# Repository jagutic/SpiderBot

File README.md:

# Spider
Proyecto final Mecatrónica

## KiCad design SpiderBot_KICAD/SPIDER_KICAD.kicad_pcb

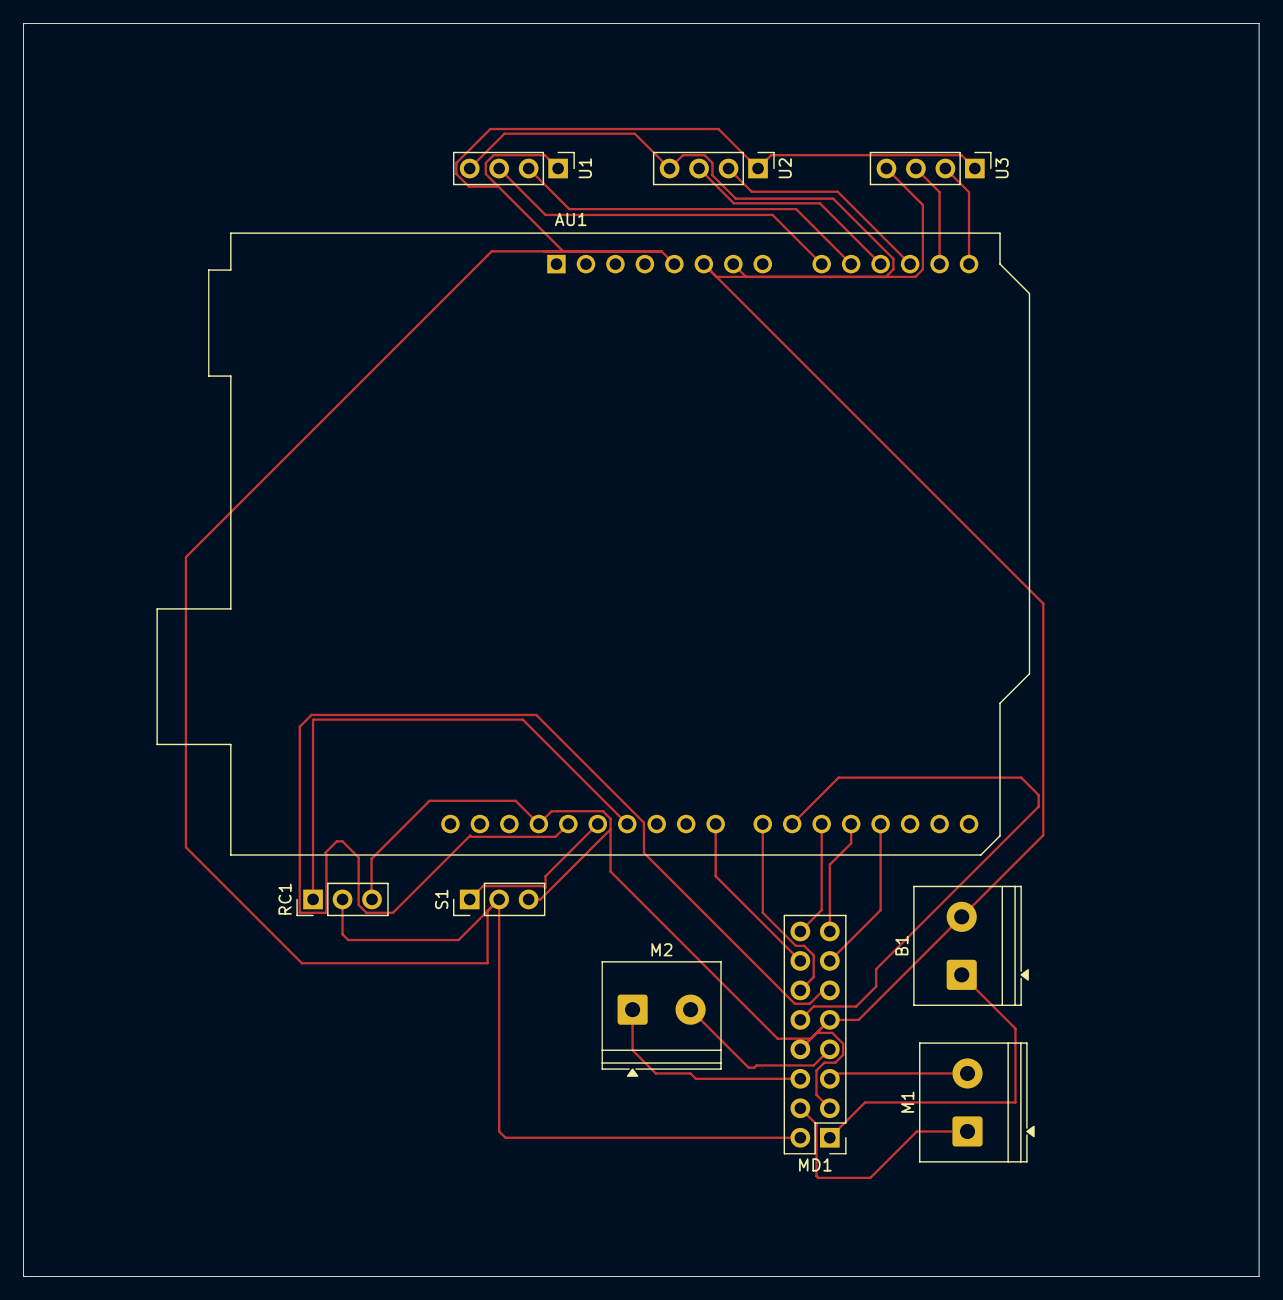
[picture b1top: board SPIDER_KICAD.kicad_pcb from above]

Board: 2 copper layers, 106.5 x 108.0 mm, 10 parts (0 on the bottom side), 22 nets.

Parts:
AU1: Arduino_UNO_R3
B1: Battery; TerminalBlock_Phoenix_PT-1,5-2-5.0-H_1x02_P5.00mm_Horizontal
M1, M2: Motor; TerminalBlock_Phoenix_PT-1,5-2-5.0-H_1x02_P5.00mm_Horizontal
MD1: Motor Driver (TB6612FNG); PinHeader_2x08_P2.54mm_Vertical
RC1: Remote Controller; PinHeader_1x03_P2.54mm_Vertical
S1: Servomotor; PinHeader_1x03_P2.54mm_Vertical
U1, U2, U3: Ultrasonic Sensor (HC-SR04); PinHeader_1x04_P2.54mm_Vertical

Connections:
+5V: AU1.5 (+5V), MD1.2, RC1.2, S1.2, U1.1, U2.1, U3.1
AIN1: AU1.23 (D8), MD1.14
AIN2: AU1.19 (D4), MD1.15
BIN1: AU1.18 (D3), MD1.13
BIN2: AU1.28 (D13), MD1.11
ECHO1: AU1.9 (A0), U1.3
ECHO2: AU1.11 (A2), U2.3
ECHO3: AU1.13 (SDA/A4), U3.3
GND: AU1.6 (GND), AU1.7 (GND), AU1.29 (GND), B1.2, MD1.3, MD1.8, MD1.9, RC1.3, S1.3, U1.4, U2.4, U3.4
IR_DATA: AU1.26 (D11), RC1.1
MSTBY: AU1.22 (D7), MD1.12
unnamed: M1.1, MD1.4
unnamed: M1.2, MD1.5
unnamed: M2.1, MD1.6
unnamed: M2.2, MD1.7
PWMA: AU1.20 (D5), MD1.16
PWMB: AU1.21 (D6), MD1.10
SERVO_PWM: AU1.27 (D12), S1.1
TRIG1: AU1.10 (A1), U1.2
TRIG2: AU1.12 (A3), U2.2
TRIG3: AU1.14 (SCL/A5), U3.2
V_BATT: B1.1, MD1.1

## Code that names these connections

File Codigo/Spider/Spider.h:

#ifndef SPIDER_H
#define SPIDER_H

#include <Servo.h>

// PINS
#define PWMA 5
#define AIN1 8
#define AIN2 4
#define PWMB 6
#define BIN1 3
#define BIN2 13
#define MOTORS_STBY 7
#define SERVO_HEAD 12

// Ultrasound sensors
#define ECHO_HEAD A0
#define TRIG_HEAD A1
#define ECHO_LEFT A2
#define TRIG_LEFT A3
#define ECHO_RIGHT A4
#define TRIG_RIGHT A5
#define MAX_DISTANCE 400.0 // cm
#define MIN_DISTANCE 2.0 // cm

// CONSTANTS
#define SPEED_MOVE 200
#define SPEED_TURN 255
#define SPEED_TURN_FACTOR 0.9
#define INIT_ANGLE 75


// Movement
const int MOTOR_LEFT[3] = {AIN2, AIN1, PWMA};
const int MOTOR_RIGHT[3] = {BIN1, BIN2, PWMB};

enum direction {
  FORWARD = 0,
  BACKWARD,
  LEFT,
  RIGHT,
};


// Class of our robot
class Spider {
private:
  Servo servo;

  // FUNCTIONS
  // Return distance in cm
  float get_dist(int trig, int echo) {
    // Clean
    digitalWrite(trig, LOW);
    delayMicroseconds(2);

    // Send trig
    digitalWrite(trig, HIGH);
    delayMicroseconds(10);
    digitalWrite(trig, LOW);

    // Calculate distance
    float duration = pulseIn(echo, HIGH, 30000);
    float dist = duration * 0.034 / 2;

    //Return error with very low values
    // or with very HIGH ones
    if (dist < MIN_DISTANCE || dist > MAX_DISTANCE) {
      //dist = get_dist(trig, echo);
      return MAX_DISTANCE;
    }

    // Reactivate when valid dist is obtained
    return dist;
  }

public:
  Spider() {
    // Set pins
    pinMode(MOTORS_STBY, OUTPUT);
    pinMode(MOTOR_LEFT[0], OUTPUT);
    pinMode(MOTOR_LEFT[1], OUTPUT);
    pinMode(MOTOR_RIGHT[0], OUTPUT);
    pinMode(MOTOR_RIGHT[1], OUTPUT);
  
    // us pins
    pinMode(TRIG_LEFT, OUTPUT);
    pinMode(TRIG_RIGHT, OUTPUT);
    pinMode(TRIG_HEAD, OUTPUT);
    pinMode(ECHO_LEFT, INPUT);
    pinMode(ECHO_RIGHT, INPUT);
    pinMode(ECHO_HEAD, INPUT);
  }


  // GETTERS
  float get_dist_head() {
    return get_dist(TRIG_HEAD, ECHO_HEAD);
  }
  float get_dist_left() {
    return get_dist(TRIG_LEFT, ECHO_LEFT);
  }
  float get_dist_right() {
    return get_dist(TRIG_RIGHT, ECHO_RIGHT);
  }


  // SERVO FUNCTIONS
  void head_set_to(int angle) {
    if (!servo.attached()) { // Si está desconectado, conéctalo
        servo.attach(SERVO_HEAD);
    }
    servo.write(angle);
  }


  // INIT / STOP
  void init_all(bool reset_head) {
    digitalWrite(MOTORS_STBY, HIGH);
    set_speed(0, 0);

    // Move servo to original pos
    servo.attach(SERVO_HEAD);
    if (reset_head) {
      head_set_to(INIT_ANGLE);
    }
  }

  // Stop motors, can reset servo pos too
  void stop_all(bool reset_head) {
    digitalWrite(MOTORS_STBY, LOW);
    set_speed(0, 0);

    digitalWrite(MOTOR_LEFT[0], LOW);
    digitalWrite(MOTOR_LEFT[1], LOW);
    digitalWrite(MOTOR_RIGHT[0], LOW);
    digitalWrite(MOTOR_RIGHT[1], LOW);

    // Move servo to original pos
    if (reset_head) {
      head_set_to(INIT_ANGLE);
    }
    servo.detach();
  }

  // set 'speed' speed
  void set_speed(int speed_left, int speed_right) {
    analogWrite(MOTOR_LEFT[2], speed_left * SPEED_TURN_FACTOR);
    analogWrite(MOTOR_RIGHT[2], speed_right);
  }

  void stop() {
    set_speed(0, 0);
    
    digitalWrite(MOTOR_LEFT[0], LOW);
    digitalWrite(MOTOR_LEFT[1], LOW);
    digitalWrite(MOTOR_RIGHT[0], LOW);
    digitalWrite(MOTOR_RIGHT[1], LOW);
  }

  // MOVEMENT FUNCTION
  void move(enum direction dir, int speed = SPEED_MOVE) {
    set_speed(speed, speed);
    
    switch(dir) {
    case FORWARD:
      digitalWrite(MOTOR_LEFT[0], HIGH);
      digitalWrite(MOTOR_LEFT[1], LOW);
      digitalWrite(MOTOR_RIGHT[0], HIGH);
      digitalWrite(MOTOR_RIGHT[1], LOW);
      break;
    case BACKWARD:
      digitalWrite(MOTOR_LEFT[0], LOW);
      digitalWrite(MOTOR_LEFT[1], HIGH);
      digitalWrite(MOTOR_RIGHT[0], LOW);
      digitalWrite(MOTOR_RIGHT[1], HIGH);
      break;
    default:
      stop_all(false);
      Serial.println("Wrong move dir");
    }
  }

  void turn(enum direction dir, int speed = SPEED_TURN) {
    set_speed(speed, speed);
    
    switch(dir) {
    case LEFT:
      digitalWrite(MOTOR_LEFT[0], LOW);
      digitalWrite(MOTOR_LEFT[1], HIGH);
      digitalWrite(MOTOR_RIGHT[0], HIGH);
      digitalWrite(MOTOR_RIGHT[1], LOW);
      break;
    case RIGHT:
      digitalWrite(MOTOR_LEFT[0], HIGH);
      digitalWrite(MOTOR_LEFT[1], LOW);
      digitalWrite(MOTOR_RIGHT[0], LOW);
      digitalWrite(MOTOR_RIGHT[1], HIGH);
      break;
    default:
      stop_all(false);
      Serial.println("Wrong turn dir");
    }
  }
};

#endif

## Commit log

2025-12-04 Indice de informe tecnico
2026-01-03 Expand sections on mechanical and electronic design
    Added detailed sections on mechanical and electronic design, including PCB design and Arduino code structure.
2026-01-03 Adicion imagenes y carpeta kicad
2026-01-03 Update InformeTecnico with PCB manufacturing details
    Added details on PCB manufacturing and validation processes, including Gerber file generation and 3D assembly validation.
2026-01-03 Create user manual with structured sections
    Added user manual with introduction and sections.
2026-01-03 Expand user manual with usage and troubleshooting sections
    Added detailed usage instructions, maintenance tips, and troubleshooting advice for the robot.
2026-01-05 Revise maintenance procedures for SpiderBot
    Updated maintenance manual for SpiderBot, clarifying battery care, mechanical structure inspection, and troubleshooting steps.
2026-01-05 Correct typos and enhance clarity in ManualMantenimiento
    Fixed typos and improved clarity in maintenance manual.
2026-01-07 Separar en carpetas y añadir stls
2026-01-07 Borrar arcihvos movidos
2026-01-07 Changes names to readme
2026-01-07 Renombrar stls
2026-01-07 Cambiar Caja y fotos
2026-01-08 Update user manual sections and headings
2026-01-08 Adicion carpeta con imagen
2026-01-08 Insert image for IR remote control section
    Added image for IR remote control in README.
2026-01-08 Adicion nueva imagen
2026-01-08 Fix image source paths in README.md
2026-01-08 Enhance README with manual control instructions
    Added detailed instructions for manual control mode and button functions.
2026-01-08 Update README with navigation modes and controls
    Added information about intelligent navigation modes and updated control manual section.
2026-01-08 Revise README for project updates and new sections
    Updated the README to reflect changes in the project structure and design details.
2026-01-08 Enhance README with simulation and design details
    Added detailed explanation of simulation challenges and URDF limitations.
2026-01-08 Enhance README with images and detailed explanations
    Added images and improved explanations in the README.
2026-01-08 update photos
2026-01-08 Informe de Autoevaluacion
2026-01-08 Revise README with design and assembly updates
    Updated the README to reflect changes in the robot's design and assembly instructions, including modifications to the 3D models and simulation details.
2026-01-08 Adjust image widths in README.md
    Updated image sizes in README for better layout.
2026-01-08 Revise README for clarity on robot components and methods
    Updated README with detailed components and methods for robot control.
2026-01-09 Codigo sin arreglos
2026-01-09 Base y medio stl subidos
2026-01-09 simulacion
2026-01-09 Planos añadidos
2026-01-09 Rename maintenance manual to Spiderbot
2026-01-09 Fix sensor type in troubleshooting table
    Updated troubleshooting table to reflect changes in sensor type for obstacle avoidance.
2026-01-09 code updated
